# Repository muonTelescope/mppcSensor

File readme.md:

# MPPC Sensor
The sensor board has just the MPPC and a coaxial connector to feed in the high voltage and inside shielding pull the signal out. There are two mounting holes on the sides and the board is designed to be small and mounted inside a plastic carrier. An ambient temperature sensor is required to set the voltage but is not provided on the board, as the gain is dependent on temperature and bias voltage, a constant gain can be maintained by changing the bias in response to temperature.

![][renderAssembly]

## Hardware
This board houses a surface mount 2.0mm MPPC by Hamamatsu. Specifically, S13360-20**VE series. Both ports are routed directly out to the connector. The board is  0.25in (6.35) tall, 0.5in (12.7mm) wide and approximately XXin deep. It is attached to the housing with two M2 screws. 

![][renderFront]

## Cable
A U.FL coaxial connector is mounted on the back. It is rated for 50 mattings. HV is brought in through shielding (connected to cathode) and should be insulated. signal is returned (anode) through the inner conductor. The connector and the board have no polarity.

![][renderBack]

## Housing
Housing is designed in Autodesk inventor, more info later.

## Fabrication/Assembly
Documents such as gerbers, PNP, BOM, STL, images and renderings are availible in the `production` directory.

The PCB is a two sided 63mil (1.6mm) with 6/6 routing. Front and back silk and soldermask is not needed but prefered. Assembly requires PNP on two sides, but ideally should be done manually. The MPPC should be handeled delicately and its part number and parameters should be kept. After assembly place the part back in its original bag. 

### Front PCB
Only MPPC on front with though mounting holes shown. The polarity is shown with the notch visible at the bottom. 
![][frontAsy]

### Back PCB
Back has only the U.FL connector. There is only one polarity but since there are two tabs generally available on the connectors the bottom must be ckeced or the pin one cut corner to determine orientation.
![][backAsy]

### Soldering
Solder the back first (reflow or by hand) before placing and reflowing the MPPC, surface tension should be enough to hold in place for the reflow, but CA can be applied to make sure it does not shift. The MPPC ideally should be reflowed with the Hamamatsu temperature profile.
![][mppcTemp]

### Housing
The housing is to be made form a opaque material. Can be 3D printed or IM (if design permits). More infor after design.

[renderAssembly]: production/images/renderAssembly.png "Full assembly permutations inculding housings."
[renderFront]: production/images/renderFront.png "Assembled board front render showing MPPC."
[renderBack]: production/images/renderBack.png "Assembled board back render showing connector."
[frontAsy]: production/images/frontAsy.png "Component location and markings for front."
[backAsy]: production/images/backAsy.png "Assembled board back render showing connector."
[mppcTemp]: production/images/mppcTemp.png "Reflow temperature profile for Hamamatsu MPPC from datasheet."

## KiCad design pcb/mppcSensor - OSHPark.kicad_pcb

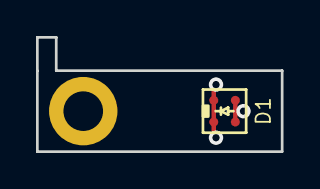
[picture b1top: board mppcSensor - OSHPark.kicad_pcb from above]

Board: 2 copper layers, 13.6 x 6.3 mm, 3 parts (1 on the bottom side), 2 nets.

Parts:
D1: S13360-2050VE
H1: MountingHole; MountingHole_2.2mm_M2_ISO14580_Pad
J1: Conn_Coaxial; U.FL_Hirose_U.FL-R-SMT-1_Vertical

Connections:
unnamed: D1.1, J1.1
unnamed: D1.2, J1.2

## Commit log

2015-09-09 Added more files
2015-09-09 Deleted V1,2,3
2015-09-09 Remove V5
2015-09-09 Removed files, and reorganised file system.
2015-09-09 Added cad files
2015-09-09 Added cad data
2015-09-09 Only left v4 cad data
2015-09-09 Refreshed file name and locations
2015-10-09 No idea what changed
2015-10-09 Resaved files
2015-10-15 Added pattren files, rebuit sensor to use modular jackes.
2015-10-15 Once more
2015-10-16 New Cad model
2015-10-16 Moved cap file
2015-10-16 Moved mounting holes down
2015-10-16 Saved layout
2015-11-05 Edge connector layout final
2015-11-05 Removed local ibraries
2015-11-05 Cad desgin done, only ethernet jack left
2015-11-05 Cad desgin done, only ethernet jack left, parts added
2015-11-06 3d files added
2015-11-09 Fixed bom
2015-11-09 single rail amp, themistor voltage readout
2015-11-09 SMD MPPC, 7mm wide pcb
2015-11-13 Fixed BOM errors, pcb approx postioning/sizing done
2016-01-19 Seperate 60V supply
2016-01-20 Max1932 Power section
2016-01-20 Headers added, Custom power supply complete
2016-01-20 Added EMI Shield, sent to fab
2016-01-23 30x7mm Amp
2016-01-23 MOved temp resistor off, moved vias arround
2016-01-23 MOre compact layout
2016-01-25 Compact assembly
2016-01-25 Reduced size, re organised connectors
2016-01-25 Finished routing attachment pcb
2016-02-15 almost ready to 3d export
2016-02-15 Cad done
2016-02-17 Added Haeader
2016-02-23 Interface board desgin started
2016-02-23 Arduino Nano, and Headers as output
2016-02-23 PLaced layout
2016-02-24 Moved some parts arround
2016-02-27 Switching branches
2016-02-28 Split into diffrent folders
2016-03-02 Sent out to fab
2016-03-09 BOM Updated
2016-03-26 Removed old files
2016-03-27 Switching Branch
2016-03-27 Moved interface Board to its own repo
2016-03-27 Renamed branch, moved interface board to its own repo
2016-03-27 Starting to work onthe readme
2016-03-27 Asteriks not bold
2016-03-28 this one has the 3mm sensor
2016-03-28 Fixed the mppc type
2016-03-28 Renamed from sensotboard
2016-03-28 Correct layout and schematic files
2016-04-02 Revert to use older Op-Amp
2016-06-01 Added Resistors for IMpedence machaing, run via through center ground pad
2016-06-15 Removed spacer rubber
2016-07-08 Added via, to remove osccilations
2016-07-08 A more reasonable readme. Also added pictures into rendergings, should be fixed at some point.
2016-08-11 Change MPPC
2016-08-11 changed cutout shape
2016-10-19 Changed decal files
2017-01-04 changed connector
2017-01-05 Rebuilt, bom still needs to be fixed.
2017-01-07 BOM fixed, REF-DES cahnged for led
2017-01-07 Removed ini file
2018-05-25 new board used on hodoscope
2018-12-11 Changed breakout layout
2019-01-13 inital commit
2019-02-23 Changed to kicad, sensor only boards
2019-02-23 Remove files updated ignore
2019-02-23 Removed bakcup componet file
2019-02-23 Moved files to pcb folder
2019-02-23 Updated readme with new design, added renderings.
2019-02-23 Fixed harware section, added temp img
2019-02-23 Added cad dir
2022-10-26 oldBoard snapshot
2022-10-26 Removed old files updated libraries
2022-10-26 Modified board to oshpark req .25x.25
